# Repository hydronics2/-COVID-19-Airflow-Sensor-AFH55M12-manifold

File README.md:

#### This project is similar to the project using the standalone sensor described here: [AFH55M12](https://github.com/hydronics2/COVID-19-Airflow-Sensor-AFH55M12)

# Automotive Airflow Sensor (AFH55M12) in a manifold configuration

Picture. Manifold by Patrick Campbell with Tee Fittings modified to accept airflow sensors.

## Project Description ([from Helpful Engineering](https://www.helpfulengineering.org/))
The intent here is to create a monitoring device, based on a mass airflow meter, that can be used when splitting a ventilator into two or more patients. This will allow staff to monitor individual patients while being controlled by one device in extreme situations where the number of ventilators are not enough to handle the number of patients. The readout should be visible locally on the device and there may need to be parameters input by staff to create a safe operating range and to possibly create alarms when the system is measuring an out of range parameter.

### [Project Requirements](https://docs.google.com/document/d/17Ps910A2vRwnM4EM6F-71GNG1XNa0PaeImd53F7428c/edit?usp=sharing)

This is a quick study of using an inexpensive off-the-shelf automotive airflow type sensor.

Reading from an automotive mass airflow sensor using a microController 12bit ADC, 20ms interval

### --- Updates April 24th -- Assembled PCB, airflow sensor

### Teensy pins
- pin 0 - user led
- pin 1 - error led
- pin 23 - buzzer
- pin A0 - flow sensor pin
- pin 20 - encoder A
- pin 21 - encoder B
- pin 22 - encoder button
- pin 5 - button

### Sensor Availability
The sensor shows up as multiple part values. It fits a 1998 Nissan/Datsun Truck Frontier 2WD 2.4L FI 4cyl among other years and other vehicles.
- [China](https://www.aliexpress.com/item/32989444018.html?spm=a2g0o.cart.0.0.74dd3c00g1XL5u&mp=1)
- [US Supplier](https://www.amazon.com/gp/product/B074FZMGWG/ref=ppx_yo_dt_b_asin_title_o00_s00?ie=UTF8&psc=1)
- [local supplier oreilly](https://www.oreillyauto.com/search/1998/nissan/frontier?q=MF21219)
- [local supplier auto-zone](https://www.autozone.com/engine-management/mass-air-flow-sensor/duralast-new-mass-air-flow-sensor-dl-3025/337334_0_4995?&searchText=DL3025)

#### Pinout
- Pin A - Empty
- Pin B - 7-12V DC, 90-115mA
- Pin C - Ground
- Pin D Signal

#### Parts List
- microController - [Teensy 4.0](https://www.pjrc.com/store/teensy40.html)
- display - [2.8" TFT 320x240 display](https://www.pjrc.com/store/display_ili9341_touch.html)
- BME280 pressure sensor [828-1063-1-ND](https://www.digikey.com/product-detail/en/bosch-sensortec/BME280/828-1063-1-ND/6136314)

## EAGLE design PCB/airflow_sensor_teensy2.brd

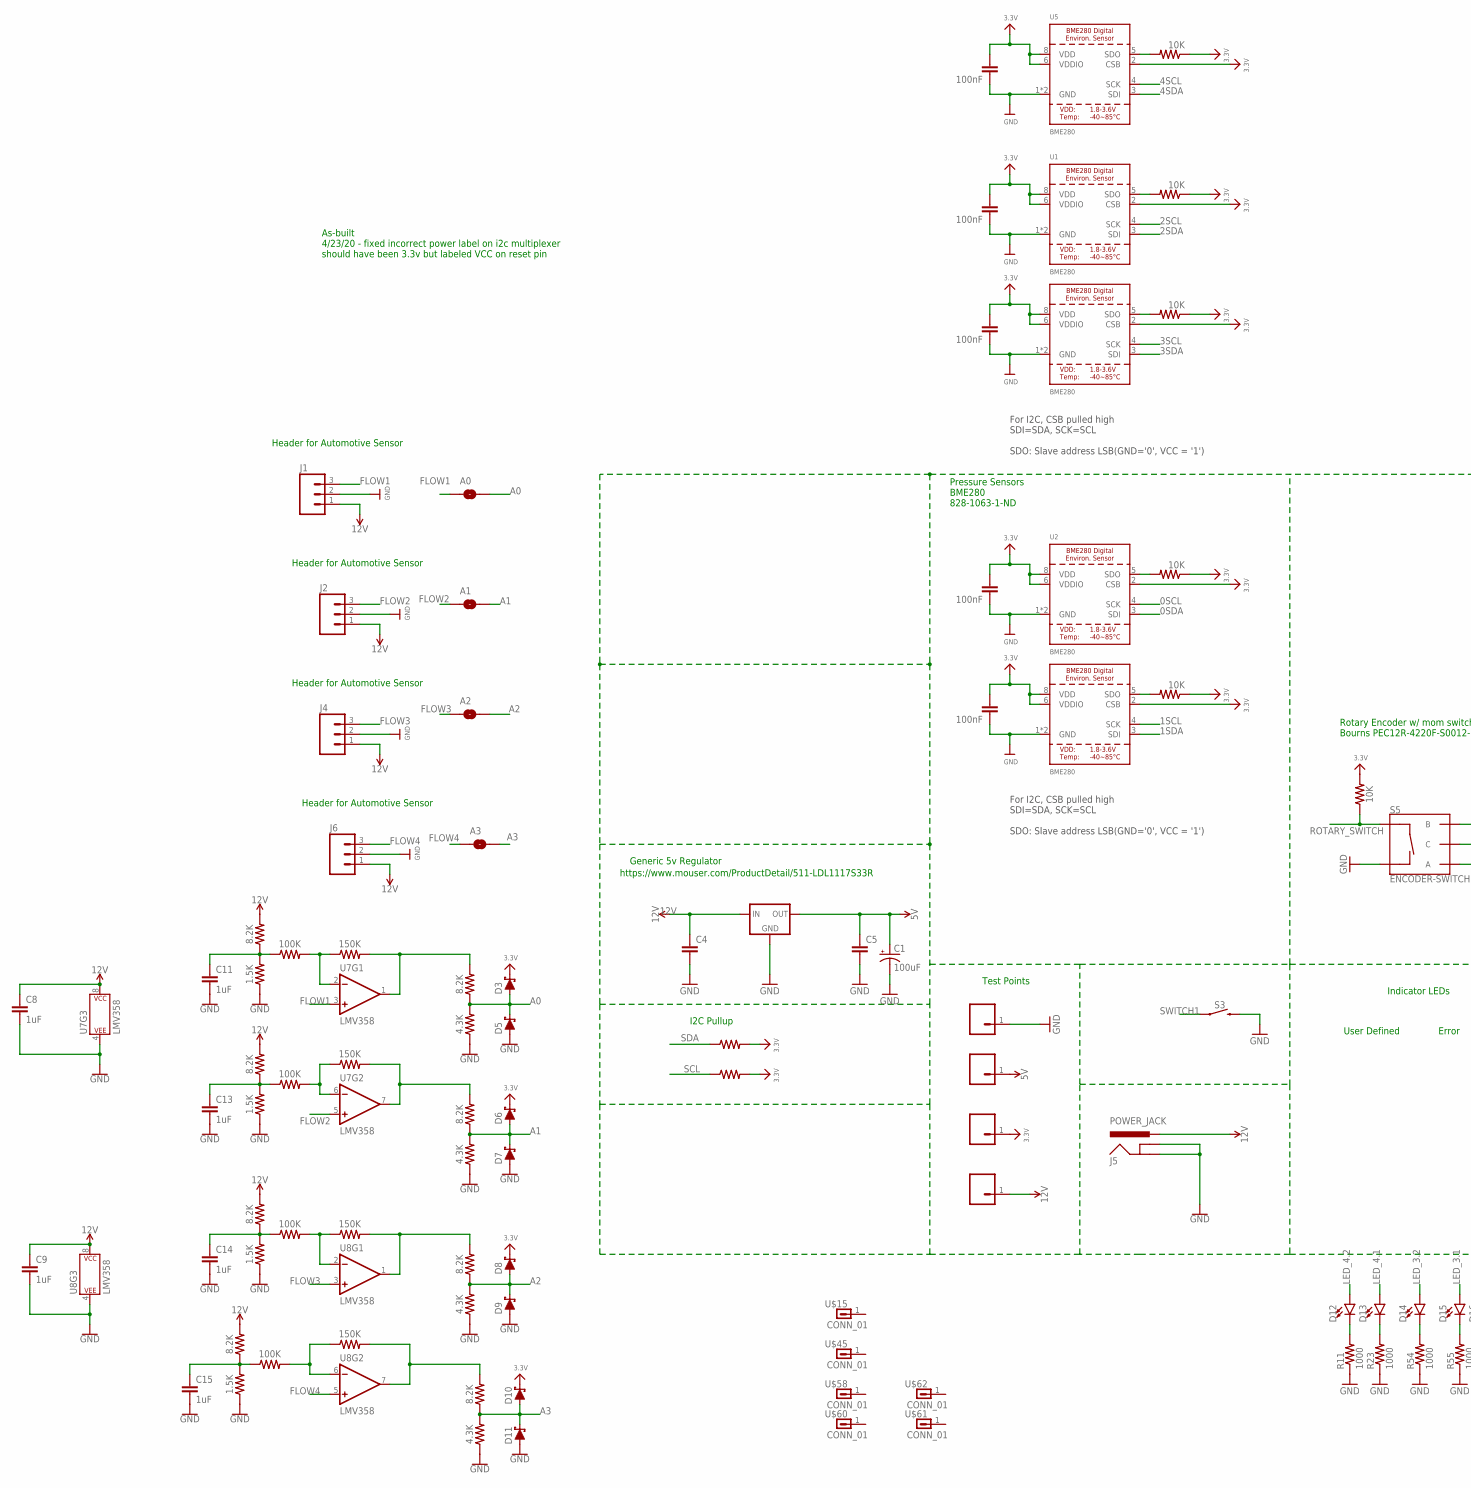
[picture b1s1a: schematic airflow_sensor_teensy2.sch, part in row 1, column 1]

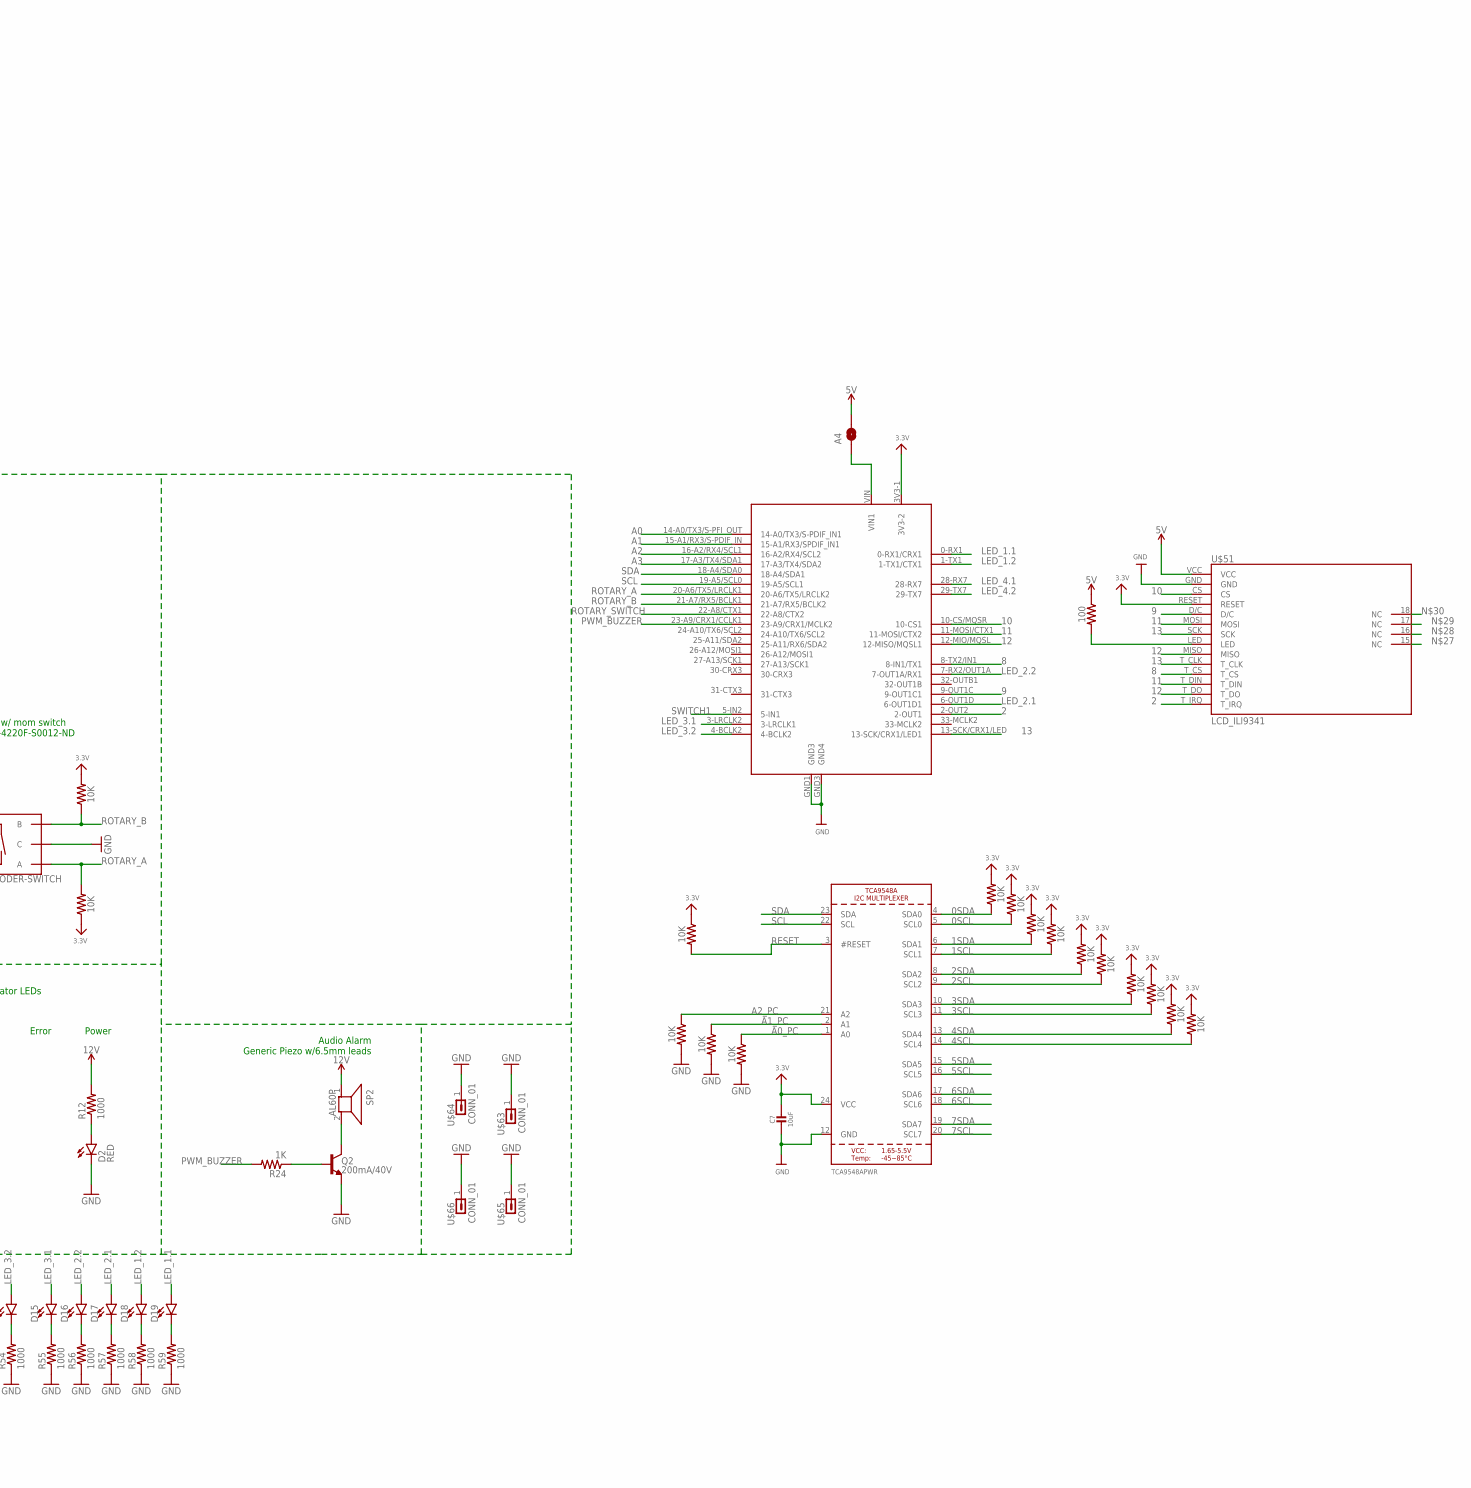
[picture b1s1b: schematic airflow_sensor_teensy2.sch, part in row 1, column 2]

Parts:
3V_REGULATOR: LDL1117_5V_REG; SOT223
A0, A1, A2, A3, A4: JUMPER-SMT_2_NO_NO-SILK; SMT-JUMPER_2_NO_NO-SILK
C1: 100uF; CPOL-RADIAL-2.5MM-6.5MM
C2, C3, C6, C10, C12: 100nF; 0805
C4, C5: CAP-0805; 0805
C7: 10uF; 0805-NO
C8, C9, C11, C13, C14, C15: 1uF; 0805
D2: RED; LED-1206
D3, D5, D6, D7, D8, D9, D10, D11: 3A/40V/500mV; SMA-DIODE
D12, D13, D14, D15, D16, D17, D18, D19: LED5MM; LED_5MM
J1, J2, J4, J6: M03SCREW; SCREWTERMINAL-3.5MM-3
J5: POWER_JACK; POWER_JACK_PTH
Q2: 200mA/40V; TO-92
R1, R2, R3, R4, R5, R6, R7, R8, R9, R10, R13, R14, R15, R16, R17, R18, R19, R20, R25, R26, R27, R28: 10K; 0805
R11, R12, R23, R54, R55, R56, R57, R58, R59: 1000; 0805
R21, R22: 0.3; 0805
R24: 1K; 0805
R29, R30, R31, R32: 150K; 0805
R33, R35, R37, R39: 4.3K; 0805
R34, R36, R38, R40, R41, R44, R47, R50: 8.2K; 0805
R42, R45, R48, R51: 1.5K; 0805
R43, R46, R49, R52: 100K; 0805
R53: 100; 0805
S3: MOMENTARY-SWITCH-SPST-PTH-6.0MM-KIT; TACTILE_SWITCH_PTH_6.0MM_KIT
S5: ENCODER-SWITCH; ROTARY_ENC_PLAIN
SP2: AL60P
U1, U2, U3, U4, U5: BME280
U6: TCA9548APWR; TSSOP24
U7, U8: LMV358; SO08
U$15, U$45, U$58, U$60, U$61, U$62, U$63, U$64, U$65, U$66: CONN_01; 1X01-#6_MACHINE
U$20, U$31, U$40, U$59: CONN_0138MILL; 1X01-40MILL
U$51: LCD_ILI9341; ILI9341
U$67: TEENSY_ALL_PINS; TEENSY4-ALL_PINS

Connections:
0SCL: R8.1, U2.4 (SCK), U6.5 (SCL0)
0SDA: R7.1, U2.3 (SDI), U6.4 (SDA0)
1SCL: R10.1, U4.4 (SCK), U6.7 (SCL1)
1SDA: R9.1, U4.3 (SDI), U6.6 (SDA1)
2: U$51.T_IRQ, U$67.2-OUT2 (2-OUT1)
2SCL: R14.1, U1.4 (SCK), U6.9 (SCL2)
2SDA: R13.1, U1.3 (SDI), U6.8 (SDA2)
3.3V: C2.1, C3.1, C6.1, C7.1, C10.1, C12.1, D3.C, D6.C, D8.C, D10.C, R1.1, R2.1, R3.1, R4.1, R5.1, R6.1, R7.2, R8.2, R9.2, R10.2, R13.2, R14.2, R15.2, R16.2, R17.2, R18.2, R21.2, R22.2, R26.2, R27.1, R28.2, U1.2 (CSB), U1.6 (VDDIO), U1.8 (VDD), U2.2 (CSB), U2.6 (VDDIO), U2.8 (VDD), U3.2 (CSB), U3.6 (VDDIO), U3.8 (VDD), U4.2 (CSB), U4.6 (VDDIO), U4.8 (VDD), U5.2 (CSB), U5.6 (VDDIO), U5.8 (VDD), U6.24 (VCC), U$20.1, U$51.RESET, U$67.3V3-1 (3V3-2)
3SCL: R16.1, U3.4 (SCK), U6.11 (SCL3)
3SDA: R15.1, U3.3 (SDI), U6.10 (SDA3)
4SCL: R18.1, U5.4 (SCK), U6.14 (SCL4)
4SDA: R17.1, U5.3 (SDI), U6.13 (SDA4)
5SCL: U6.16 (SCL5)
5SDA: U6.15 (SDA5)
5V: 3V_REGULATOR.2 (OUT), 3V_REGULATOR.4 (OUT), A4.2, C1.1 (+), C5.1, R53.1, U$51.VCC, U$59.1
6SCL: U6.18 (SCL6)
6SDA: U6.17 (SDA6)
7SCL: U6.20 (SCL7)
7SDA: U6.19 (SDA7)
8: U$51.T_CS, U$67.8-TX2/IN1 (8-IN1/TX1)
9: U$51.D/C, U$67.9-OUT1C (9-OUT1C1)
10: U$51.CS, U$67.10-CS/MQSR (10-CS1)
11: U$51.MOSI, U$51.T_DIN, U$67.11-MOSI/CTX1 (11-MOSI/CTX2)
12: U$51.MISO, U$51.T_DO, U$67.12-MIO/MQSL (12-MISO/MQSL1)
12V: 3V_REGULATOR.3 (IN), C4.1, C8.1, C9.1, J1.1, J2.1, J4.1, J5.PWR, J6.1, R12.2, R41.2, R44.2, R47.2, R50.2, SP2.1, U7.8 (P$V+), U8.8 (P$V+), U$40.1
13: U$51.SCK, U$51.T_CLK, U$67.13-SCK/CRX1/LED (13-SCK/CRX1/LED1)
A0: A0.2, D3.A, D5.C, R33.2, R40.1, U$67.14-A0/TX3/S-PFI_OUT (14-A0/TX3/S-PDIF_IN1)
A0_PC: R19.1, U6.1 (A0)
A1: A1.2, D6.A, D7.C, R34.1, R35.2, U$67.15-A1/RX3/S-PDIF_IN (15-A1/RX3/SPDIF_IN1)
A1_PC: R20.1, U6.2 (A1)
A2: A2.2, D8.A, D9.C, R36.1, R37.2, U$67.16-A2/RX4/SCL1 (16-A2/RX4/SCL2)
A2_PC: R25.1, U6.21 (A2)
A3: A3.2, D10.A, D11.C, R38.1, R39.2, U$67.17-A3/TX4/SDA1 (17-A3/TX4/SDA2)
FLOW1: A0.1, J1.3, U7.3 (+IN)
FLOW2: A1.1, J2.3, U7.5 (+IN)
FLOW3: A2.1, J4.3, U8.3 (+IN)
FLOW4: A3.1, J6.3, U8.5 (+IN)
GND: 3V_REGULATOR.1 (GND), C1.2 (-), C2.2, C3.2, C4.2, C5.2, C6.2, C7.2, C8.2, C9.2, C10.2, C11.2, C12.2, C13.2, C14.2, C15.2, D2.C, D5.A, D7.A, D9.A, D11.A, J1.2, J2.2, J4.2, J5.GND, J5.GNDBREAK, J6.2, Q2.1 (E), R11.1, R19.2, R20.2, R23.1, R25.2, R33.1, R35.1, R37.1, R39.1, R42.1, R45.1, R48.1, R51.1, R54.1, R55.1, R56.1, R57.1, R58.1, R59.1, S3.3 (2), S5.C, S5.SW-, U1.1 (GND), U1.7 (GND), U2.1 (GND), U2.7 (GND), U3.1 (GND), U3.7 (GND), U4.1 (GND), U4.7 (GND), U5.1 (GND), U5.7 (GND), U6.12 (GND), U7.4 (P$V-), U8.4 (P$V-), U$31.1, U$51.GND, U$63.1, U$64.1, U$65.1, U$66.1, U$67.GND1 (GND3), U$67.GND3 (GND4)
LED_1.1: D19.A, U$67.0-RX1 (0-RX1/CRX1)
LED_1.2: D18.A, U$67.1-TX1 (1-TX1/CTX1)
LED_2.1: D17.A, U$67.6-OUT1D (6-OUT1D1)
LED_2.2: D16.A, U$67.7-RX2/OUT1A (7-OUT1A/RX1)
LED_3.1: D15.A, U$67.3-LRCLK2 (3-LRCLK1)
LED_3.2: D14.A, U$67.4-BCLK2
LED_4.1: D13.A, U$67.28-RX7
LED_4.2: D12.A, U$67.29-TX7
unnamed: R3.2, U1.5 (SDO)
unnamed: D2.A, R12.1
unnamed: D12.K (C), R11.2
unnamed: R4.2, U3.5 (SDO)
unnamed: R1.2, U4.5 (SDO)
unnamed: D13.K (C), R23.2
unnamed: R2.2, U2.5 (SDO)
unnamed: Q2.3 (C), SP2.2
unnamed: Q2.2 (B), R24.1
unnamed: D14.K (C), R54.2
unnamed: R5.2, U5.5 (SDO)
unnamed: D15.K (C), R55.2
unnamed: D16.K (C), R56.2
unnamed: D17.K (C), R57.2
unnamed: D18.K (C), R58.2
unnamed: D19.K (C), R59.2
unnamed: R32.2, R38.2, U8.7 (OUT)
unnamed: R32.1, R52.2, U8.6 (-IN)
unnamed: R31.2, R36.2, U8.1 (OUT)
unnamed: R31.1, R49.2, U8.2 (-IN)
unnamed: R30.2, R34.2, U7.7 (OUT)
unnamed: R30.1, R46.2, U7.6 (-IN)
unnamed: R29.2, R40.2, U7.1 (OUT)
unnamed: R29.1, R43.2, U7.2 (-IN)
unnamed: A4.1, U$67.VIN (VIN1)
unnamed: R53.2, U$51.LED
PWM_BUZZER: R24.2, U$67.23-A9/CRX1/CCLK1 (23-A9/CRX1/MCLK2)
RESET: R6.2, U6.3 (#RESET)
ROTARY_A: R27.2, S5.A, U$67.20-A6/TX5/LRCLK1 (20-A6/TX5/LRCLK2)
ROTARY_B: R26.1, S5.B, U$67.21-A7/RX5/BCLK1 (21-A7/RX5/BCLK2)
ROTARY_SWITCH: R28.1, S5.SW+, U$67.22-A8/CTX1 (22-A8/CTX2)
SCL: R22.1, U6.22 (SCL), U$67.19-A5/SCL0 (19-A5/SCL1)
SDA: R21.1, U6.23 (SDA), U$67.18-A4/SDA0 (18-A4/SDA1)
SWITCH1: S3.1, U$67.5-IN2 (5-IN1)
X4: C14.1, R47.1, R48.2, R49.1
X5: C15.1, R50.1, R51.2, R52.1
XX: C13.1, R44.1, R45.2, R46.1
XXX: C11.1, R41.1, R42.2, R43.1

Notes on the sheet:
I2C Pullup
Test Points
Indicator LEDs
Power
Error
User Defined
Audio Alarm Generic Piezo w/6.5mm leads
Rotary Encoder w/ mom switch Bourns PEC12R-4220F-S0012-ND
Generic 5v Regulator
https://www.mouser.com/ProductDetail/511-LDL1117S33R
For I2C, CSB pulled high SDI=SDA, SCK=SCL SDO: Slave address LSB(GND='0', VCC = '1')
Header for Automotive Sensor
Pressure Sensors BME280 828-1063-1-ND
As-built 4/23/20 - fixed incorrect power label on i2c multiplexer should have been 3.3v but labeled VCC on reset pin

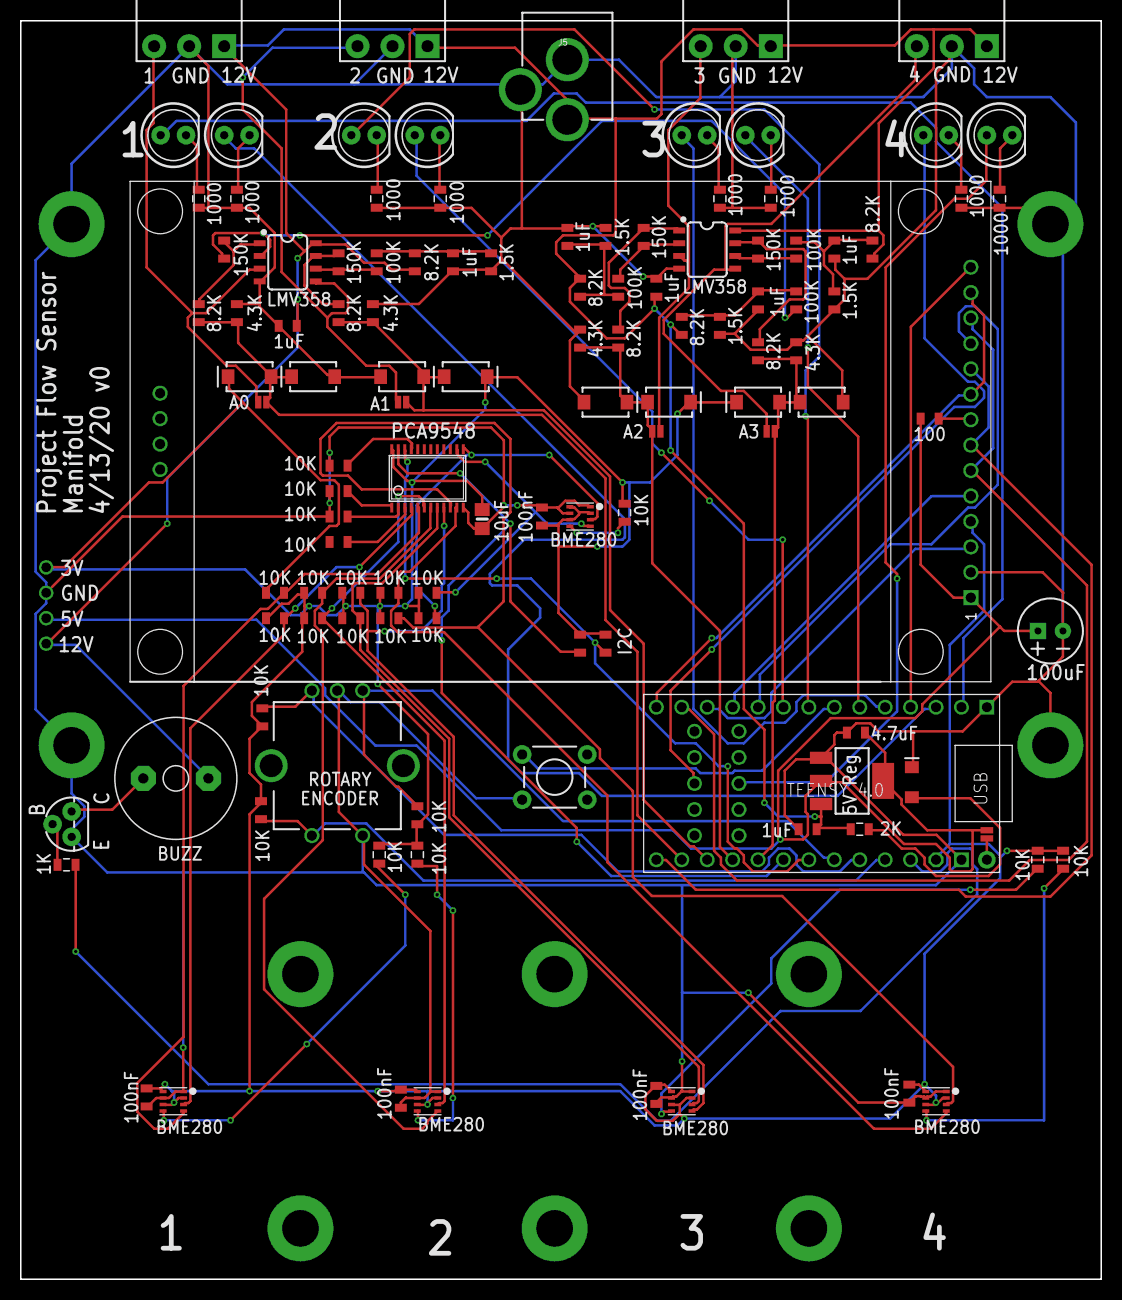
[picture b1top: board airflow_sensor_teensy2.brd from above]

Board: 2 copper layers, 108.0 x 125.7 mm, 130 parts (0 on the bottom side), 78 nets.

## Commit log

2020-04-25 test
    tested
2020-04-25 add readme
2020-04-25 added eagle files and video
2020-04-25 added arduino
2020-04-25 more pics!
2020-04-25 add manifold
2020-04-27 Realtime graph update
    (WIP) Smooth graphics test
    Working on restoring the graph visuals
    Drawing horizontal grid rules
    X and Y axis markers
    (WIP) Drawing data with bucket bridage
    Realtime graph is drawn
2020-04-27 volume
    added max volume to display
2020-04-27 pressure sensors
    update the way pressure sensors print i2c validation on startup in setup. only reading atmospheric pressure on sensor #1.

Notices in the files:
parts and their libraries:
SparkFun-Capacitors: Licensing: Creative Commons ShareAlike 4.0 International - https://creativecommons.org/licenses/by-sa/4.0
microbuilder: This work is placed in the public domain, and may be freely used for commercial and non-commercial work with the following conditions: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
